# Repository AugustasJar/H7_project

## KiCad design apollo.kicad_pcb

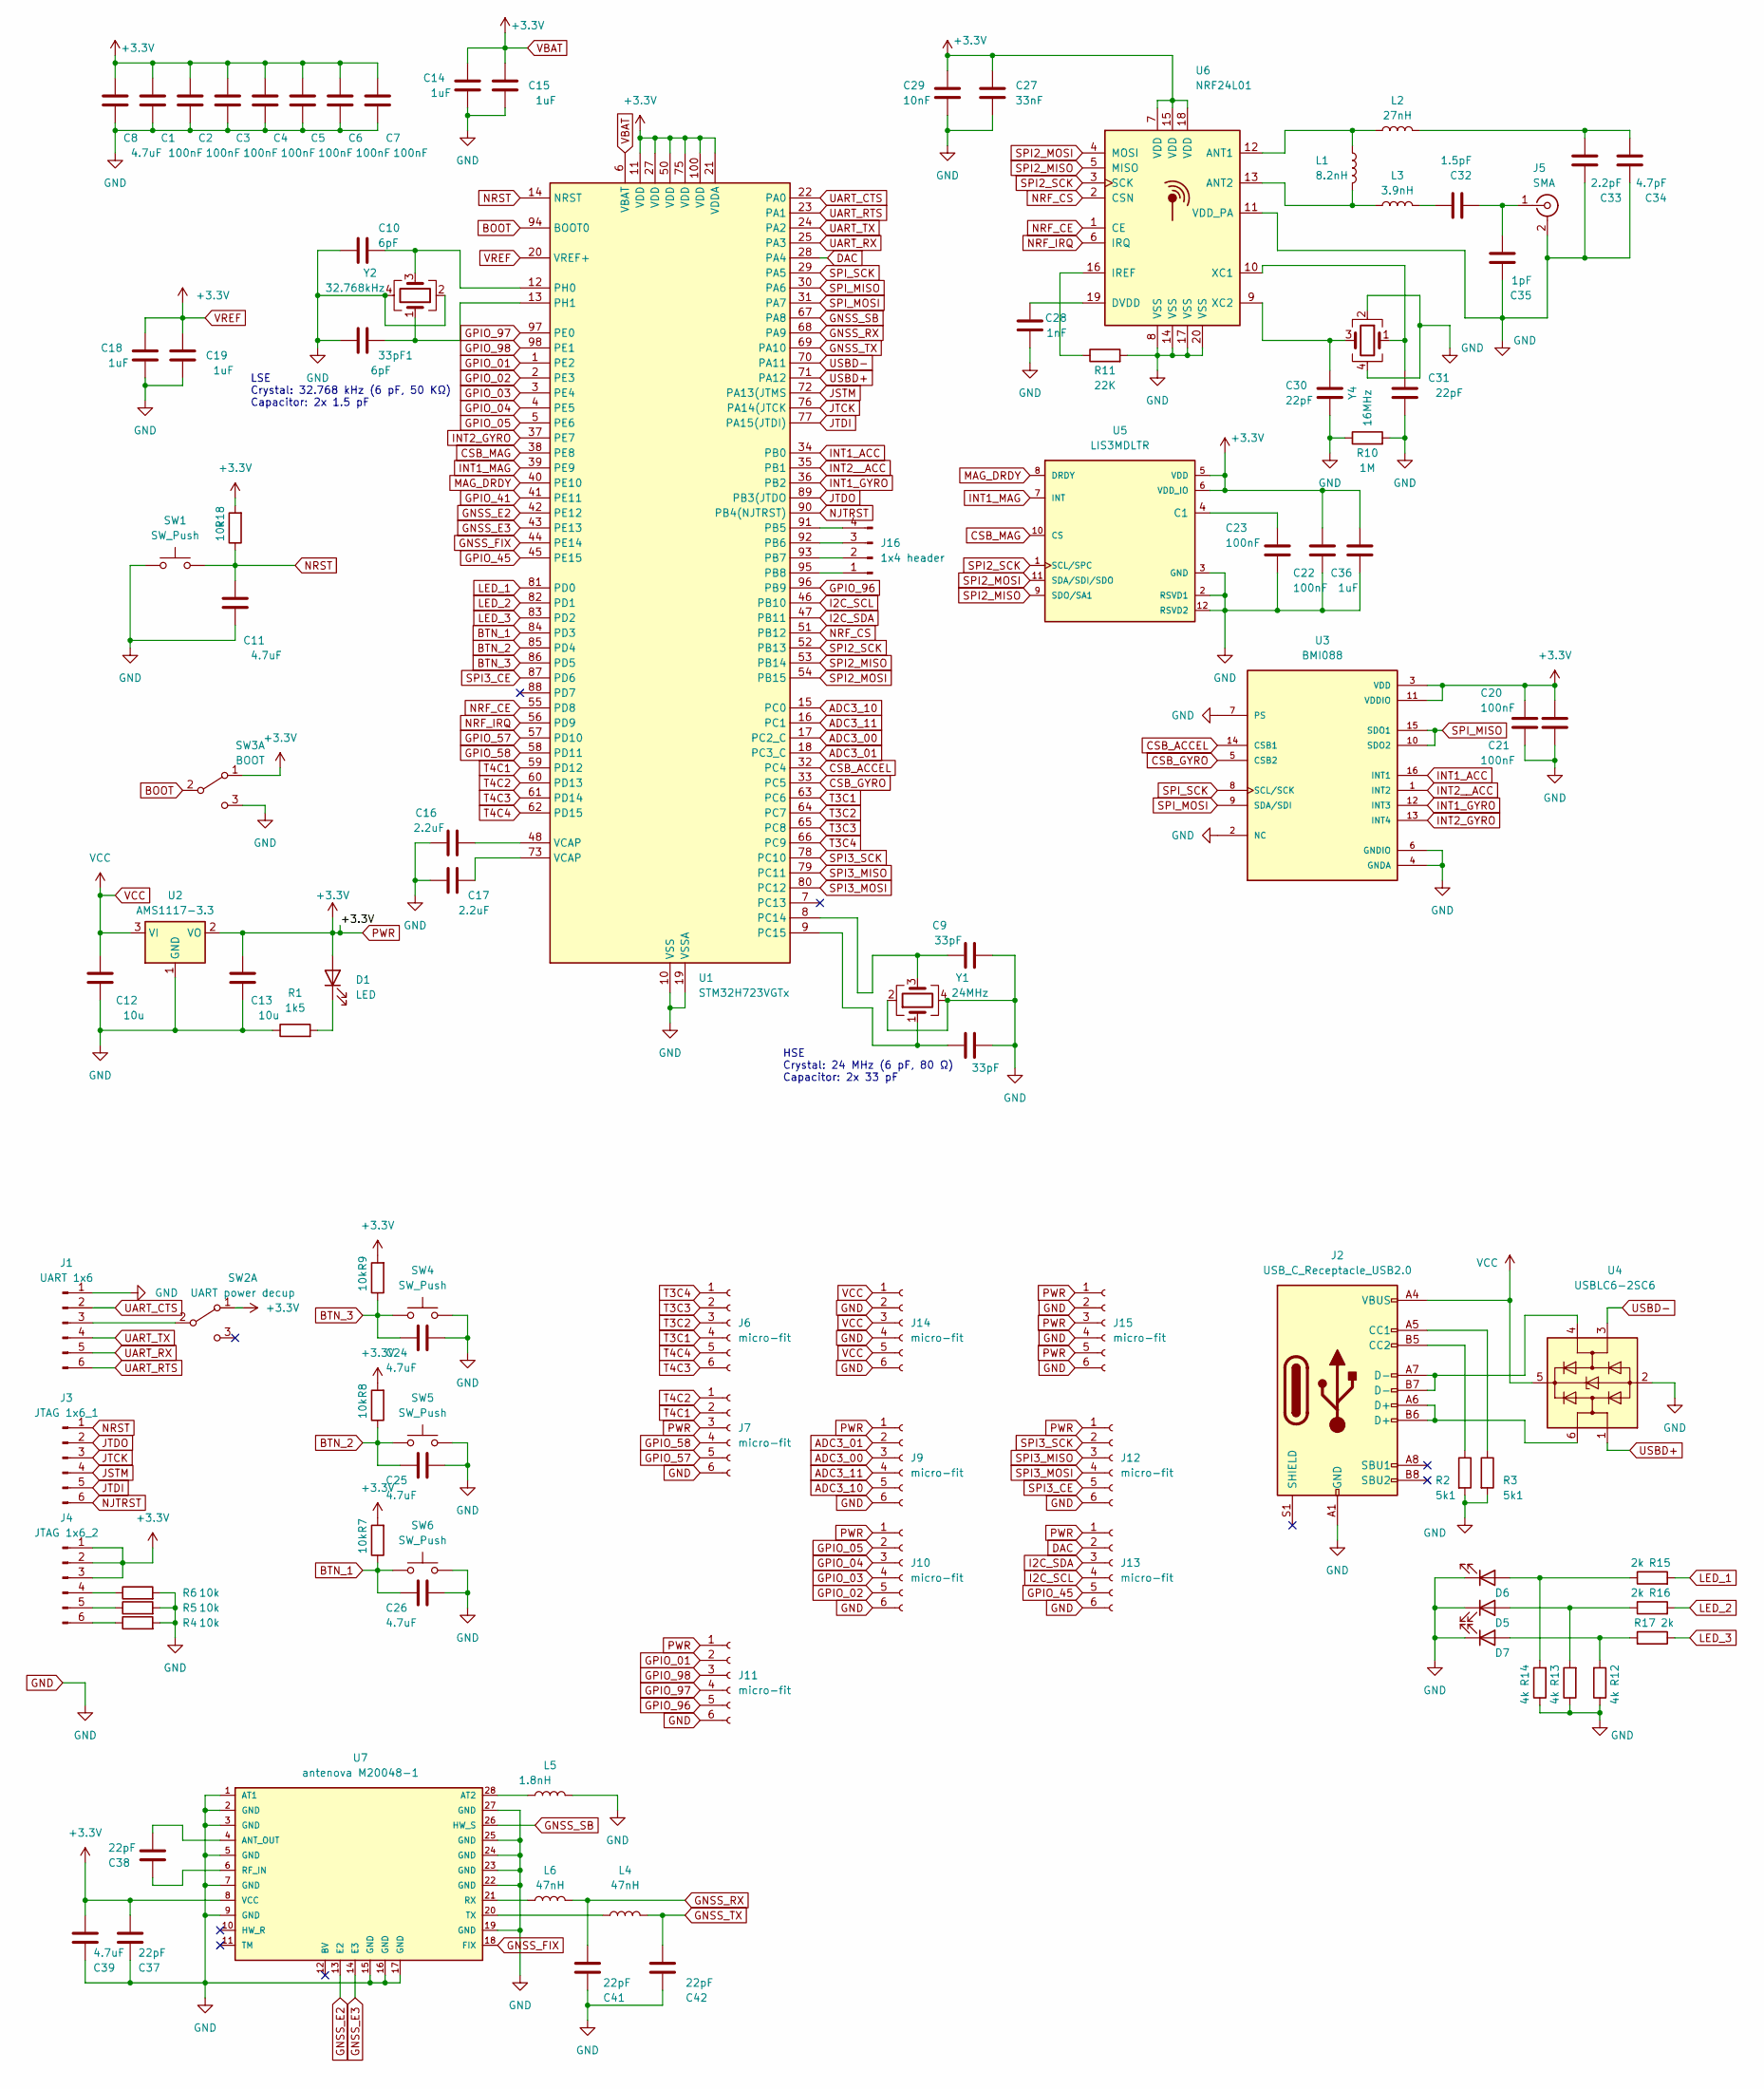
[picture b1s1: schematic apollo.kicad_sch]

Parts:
33pF1: 6pF; C_0402_1005Metric
33pF2: 33pF; C_0402_1005Metric
C1, C2, C3, C4, C5, C6, C7, C20, C21, C22, C23: 100nF; C_0402_1005Metric
C8, C11, C24, C25, C26: 4.7uF; C_0603_1608Metric
C9: 33pF; C_0402_1005Metric
C10: 6pF; C_0402_1005Metric
C12, C13: 10u; C_0603_1608Metric
C14, C15, C18, C19, C36: 1uF; C_0402_1005Metric
C16, C17: 2.2uF; C_0402_1005Metric
C27: 33nF; C_0402_1005Metric
C28: 1nF; C_0402_1005Metric
C29: 10nF; C_0402_1005Metric
C30, C31, C37, C38, C41, C42: 22pF; C_0402_1005Metric
C32: 1.5pF; C_0402_1005Metric
C33: 2.2pF; C_0402_1005Metric
C34: 4.7pF; C_0402_1005Metric
C35: 1pF; C_0402_1005Metric
C39: 4.7uF; C_0402_1005Metric
D1, D5, D6, D7: LED; LED_1206_3216Metric
J1: UART 1x6; Molex_Micro-Fit_3.0_43650-0615_1x06_P3.00mm_Vertical
J2: USB_C_Receptacle_USB2.0; USB_C_Receptacle_G-Switch_GT-USB-7010ASV
J3: JTAG 1x6_1; Molex_Micro-Fit_3.0_43650-0615_1x06_P3.00mm_Vertical
J4: JTAG 1x6_2; Molex_Micro-Fit_3.0_43650-0615_1x06_P3.00mm_Vertical
J5: SMA; SMA_Molex_73251-2200_Horizontal
J6, J7, J9, J10, J11, J12, J13, J14, J15: micro-fit; Molex_Micro-Fit_3.0_43650-0615_1x06_P3.00mm_Vertical
J16: 1x4 header; PinHeader_1x04_P2.54mm_Vertical
L1: 8.2nH; L_0402_1005Metric
L2: 27nH; L_0402_1005Metric
L3: 3.9nH; L_0402_1005Metric
L4, L6: 47nH; L_0402_1005Metric
L5: 1.8nH; L_0402_1005Metric
R1: 1k5; R_0603_1608Metric
R2, R3: 5k1; R_0603_1608Metric
R4, R5, R6, R7, R8, R9, R18: 10k; R_0603_1608Metric
R10: 1M; R_0603_1608Metric
R11: 22K; R_0603_1608Metric
R12, R13, R14: 4k; R_0603_1608Metric
R15, R16, R17: 2k; R_0603_1608Metric
SW1: SW_Push; Panasonic_EVQPUJ_EVQPUA
SW2: UART power decup; SW_DPDT_CK_JS202011JCQN
SW3: BOOT; SW_DPDT_CK_JS202011JCQN
SW4, SW5, SW6: SW_Push; K8-5851E
U1: STM32H723VGTx; LQFP-100_14x14mm_P0.5mm
U2: AMS1117-3.3; SOT-223-3_TabPin2
U3: BMI088; PQFN50P450X300X100-16N
U4: USBLC6-2SC6; SOT-23-6
U5: LIS3MDLTR; XDCR_LIS3MDLTR
U6: NRF24L01; QFN-20-1EP_4x4mm_P0.5mm_EP2.5x2.5mm
U7: antenova M20048-1; ant; PARTREV 6
Y1: 24MHz; Crystal_SMD_3225-4Pin_3.2x2.5mm
Y2: 32.768kHz; Crystal_SMD_3225-4Pin_3.2x2.5mm
Y4: 16MHz; Crystal_SMD_3225-4Pin_3.2x2.5mm

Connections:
ADC3_00: J9.3, U1.17 (PC2_C)
ADC3_01: J9.2, U1.18 (PC3_C)
ADC3_10: J9.5, U1.15 (PC0)
ADC3_11: J9.4, U1.16 (PC1)
BOOT: SW3.2 (B), U1.94 (BOOT0)
BTN_1: C26.2, R7.1, SW6.1, U1.84 (PD3)
BTN_2: C25.2, R8.1, SW5.1, U1.85 (PD4)
BTN_3: C24.2, R9.1, SW4.1, U1.86 (PD5)
CSB_ACCEL: U1.32 (PC4), U3.14 (CSB1)
CSB_GYRO: U1.33 (PC5), U3.5 (CSB2)
CSB_MAG: U1.38 (PE8), U5.10 (CS)
DAC: J13.2, U1.28 (PA4)
GND: 33pF1.2, 33pF2.2, C1.2, C2.2, C3.2, C4.2, C5.2, C6.2, C7.2, C8.2, C9.2, C10.2, C11.2, C12.2, C13.2, C14.2, C15.2, C16.1, C17.1, C18.2, C19.2, C20.2, C21.2, C22.2, C23.2, C24.1, C25.1, C26.1, C27.2, C28.2, C29.2, C30.2, C31.2, C33.1, C34.1, C35.1, C36.2, C37.2, C39.2, C41.2, C42.2, D5.1 (K), D6.1 (K), D7.1 (K), J1.1, J2.A1 (GND), J2.A12 (GND), J2.B1 (GND), J2.B12 (GND), J5.2 (Ext), J7.6, J9.6, J10.6, J11.6, J12.6, J13.6, J14.2, J14.4, J14.6, J15.2, J15.4, J15.6, L5.2, R1.1, R2.2, R3.2, R4.2, R5.2, R6.2, R10.1, R10.2, R11.2, R12.1, R13.1, R14.1, SW1.1, SW3.3 (C), SW4.2, SW5.2, SW6.2, U1.10 (VSS), U1.19 (VSSA), U1.26 (VSS), U1.49 (VSS), U1.74 (VSS), U1.99 (VSS), U2.1 (GND), U3.2 (NC), U3.4 (GNDA), U3.6 (GNDIO), U3.7 (PS), U4.2 (GND), U5.2 (RSVD1), U5.3 (GND), U5.12 (RSVD2), U6.8 (VSS), U6.11 (VDD_PA), U6.14 (VSS), U6.17 (VSS), U6.20 (VSS), U7.1 (AT1), U7.2 (GND), U7.3 (GND), U7.5 (GND), U7.7 (GND), U7.9 (GND), U7.15 (GND), U7.16 (GND), U7.17 (GND), U7.19 (GND), U7.22 (GND), U7.23 (GND), U7.24 (GND), U7.25 (GND), U7.27 (GND), Y1.2, Y1.4, Y2.2, Y2.4, Y4.2, Y4.4
GNSS_E2: U1.42 (PE12), U7.13 (E2)
GNSS_E3: U1.43 (PE13), U7.14 (E3)
GNSS_FIX: U1.44 (PE14), U7.18 (FIX)
GNSS_RX: C41.1, L6.2, U1.68 (PA9)
GNSS_SB: U1.67 (PA8), U7.26 (HW_S)
GNSS_TX: C42.1, L4.2, U1.69 (PA10)
GPIO_01: J11.2, U1.1 (PE2)
GPIO_02: J10.5, U1.2 (PE3)
GPIO_03: J10.4, U1.3 (PE4)
GPIO_04: J10.3, U1.4 (PE5)
GPIO_05: J10.2, U1.5 (PE6)
GPIO_41: U1.41 (PE11)
GPIO_45: J13.5, U1.45 (PE15)
GPIO_57: J7.5, U1.57 (PD10)
GPIO_58: J7.4, U1.58 (PD11)
GPIO_96: J11.5, U1.96 (PB9)
GPIO_97: J11.4, U1.97 (PE0)
GPIO_98: J11.3, U1.98 (PE1)
I2C_SCL: J13.4, U1.46 (PB10)
I2C_SDA: J13.3, U1.47 (PB11)
INT1_ACC: U1.34 (PB0), U3.16 (INT1)
INT1_GYRO: U1.36 (PB2), U3.12 (INT3)
INT1_MAG: U1.39 (PE9), U5.7 (INT)
INT2_GYRO: U1.37 (PE7), U3.13 (INT4)
INT2__ACC: U1.35 (PB1), U3.1 (INT2)
JSTM: J3.4, U1.72 (PA13(JTMS)
JTCK: J3.3, U1.76 (PA14(JTCK)
JTDI: J3.5, U1.77 (PA15(JTDI))
JTDO: J3.2, U1.89 (PB3(JTDO)
LED_1: R15.2, U1.81 (PD0)
LED_2: R16.2, U1.82 (PD1)
LED_3: R17.1, U1.83 (PD2)
MAG_DRDY: U1.40 (PE10), U5.8 (DRDY)
NJTRST: J3.6, U1.90 (PB4(NJTRST))
NRF_CE: U1.55 (PD8), U6.1 (CE)
NRF_CS: U1.51 (PB12), U6.2 (CSN)
NRF_IRQ: U1.56 (PD9), U6.6 (IRQ)
NRST: C11.1, J3.1, R18.1, SW1.2, U1.14 (NRST)
unnamed: C16.2, U1.48 (VCAP)
unnamed: C17.2, U1.73 (VCAP)
unnamed: C32.1, L3.2
unnamed: C33.2, C34.2, L2.2
unnamed: D1.1 (K), R1.2
unnamed: D5.2 (A), R14.2, R15.1
unnamed: D6.2 (A), R13.2, R16.1
unnamed: D7.2 (A), R12.2, R17.2
unnamed: J1.3, SW2.2 (B)
unnamed: J2.A5 (CC1), R3.1
unnamed: J2.B5 (CC2), R2.1
unnamed: J2.A6 (D+), J2.B6 (D+), U4.6 (I/O1)
unnamed: J2.A7 (D-), J2.B7 (D-), U4.4 (I/O2)
unnamed: J4.4, R6.1
unnamed: J4.5, R5.1
unnamed: J4.6, R4.1
unnamed: C32.2, C35.2, J5.1 (In)
unnamed: J16.1, U1.95 (PB8)
unnamed: J16.2, U1.93 (PB7)
unnamed: J16.3, U1.92 (PB6)
unnamed: J16.4, U1.91 (PB5)
unnamed: C9.1, U1.8 (PC14), Y1.3
unnamed: 33pF2.1, U1.9 (PC15), Y1.1
unnamed: C10.1, U1.12 (PH0), Y2.3
unnamed: 33pF1.1, U1.13 (PH1), Y2.1
unnamed: C23.1, U5.4 (C1)
unnamed: L1.1, L2.1, U6.12 (ANT1)
unnamed: L1.2, L3.1, U6.13 (ANT2)
unnamed: C28.1, U6.19 (DVDD)
unnamed: R11.1, U6.16 (IREF)
unnamed: C31.1, U6.10 (XC1), Y4.1
unnamed: C30.1, U6.9 (XC2), Y4.3
unnamed: C38.1, U7.4 (ANT_OUT)
unnamed: L5.1, U7.28 (AT2)
unnamed: C38.2, U7.6 (RF_IN)
unnamed: L6.1, U7.21 (RX)
unnamed: L4.1, U7.20 (TX)
PWR: C1.1, C2.1, C3.1, C4.1, C5.1, C6.1, C7.1, C8.1, C13.1, C14.1, C15.1, C18.1, C19.1, C20.1, C21.1, C22.1, C27.1, C29.1, C36.1, C37.1, C39.1, D1.2 (A), J4.1, J4.2, J4.3, J7.3, J9.1, J10.1, J11.1, J12.1, J13.1, J15.1, J15.3, J15.5, R7.2, R8.2, R9.2, R18.2, SW2.1 (A), SW3.1 (A), U1.6 (VBAT), U1.11 (VDD), U1.20 (VREF+), U1.21 (VDDA), U1.27 (VDD), U1.50 (VDD), U1.75 (VDD), U1.100 (VDD), U2.2 (VO), U3.3 (VDD), U3.11 (VDDIO), U5.5 (VDD), U5.6 (VDD_IO), U6.7 (VDD), U6.15 (VDD), U6.18 (VDD), U7.8 (VCC)
SPI2_MISO: U1.53 (PB14), U5.9 (SDO/SA1), U6.5 (MISO)
SPI2_MOSI: U1.54 (PB15), U5.11 (SDA/SDI/SDO), U6.4 (MOSI)
SPI2_SCK: U1.52 (PB13), U5.1 (SCL/SPC), U6.3 (SCK)
SPI3_CE: J12.5, U1.87 (PD6)
SPI3_MISO: J12.3, U1.79 (PC11)
SPI3_MOSI: J12.4, U1.80 (PC12)
SPI3_SCK: J12.2, U1.78 (PC10)
SPI_MISO: U1.30 (PA6), U3.10 (SDO2), U3.15 (SDO1)
SPI_MOSI: U1.31 (PA7), U3.9 (SDA/SDI)
SPI_SCK: U1.29 (PA5), U3.8 (SCL/SCK)
T3C1: J6.4, U1.63 (PC6)
T3C2: J6.3, U1.64 (PC7)
T3C3: J6.2, U1.65 (PC8)
T3C4: J6.1, U1.66 (PC9)
T4C1: J7.2, U1.59 (PD12)
T4C2: J7.1, U1.60 (PD13)
T4C3: J6.6, U1.61 (PD14)
T4C4: J6.5, U1.62 (PD15)
UART_CTS: J1.2, U1.22 (PA0)
UART_RTS: J1.6, U1.23 (PA1)
UART_RX: J1.5, U1.25 (PA3)
UART_TX: J1.4, U1.24 (PA2)
USBD+: U1.71 (PA12), U4.1 (I/O1)
USBD-: U1.70 (PA11), U4.3 (I/O2)
VCC: C12.1, J2.A4 (VBUS), J2.A9 (VBUS), J2.B4 (VBUS), J2.B9 (VBUS), J14.1, J14.3, J14.5, U2.3 (VI), U4.5 (VBUS)

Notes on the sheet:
HSE Crystal: 24 MHz (6 pF, 80 Ω) Capacitor: 2x 33 pF
LSE Crystal: 32.768 kHz (6 pF, 50 KΩ) Capacitor: 2x 1.5 pF

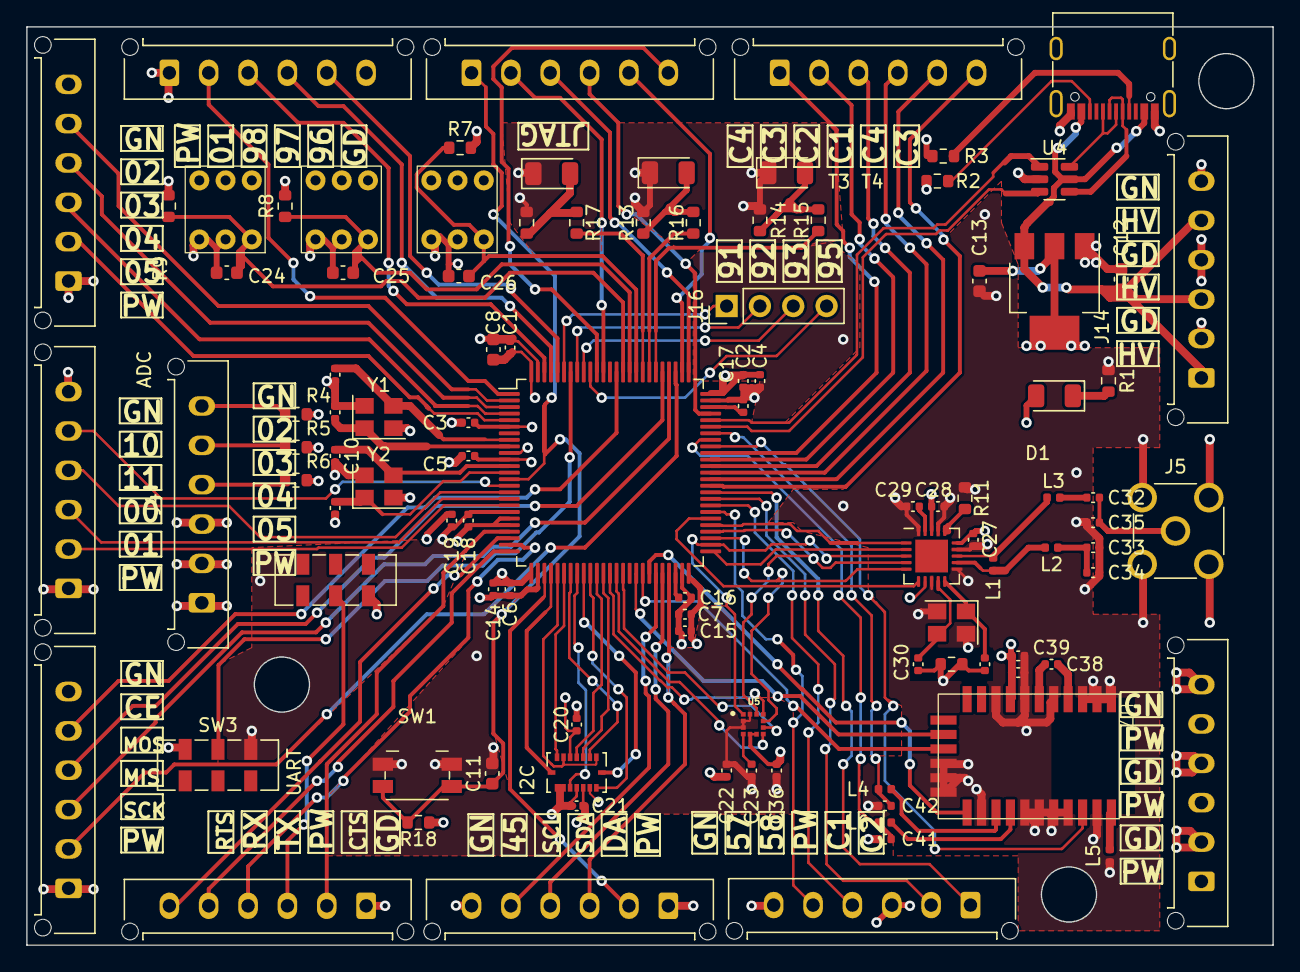
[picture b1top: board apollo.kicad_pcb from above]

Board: 4 copper layers, 95.0 x 70.0 mm, 102 parts (0 on the bottom side), 113 nets.

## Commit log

2024-01-04 init commit
